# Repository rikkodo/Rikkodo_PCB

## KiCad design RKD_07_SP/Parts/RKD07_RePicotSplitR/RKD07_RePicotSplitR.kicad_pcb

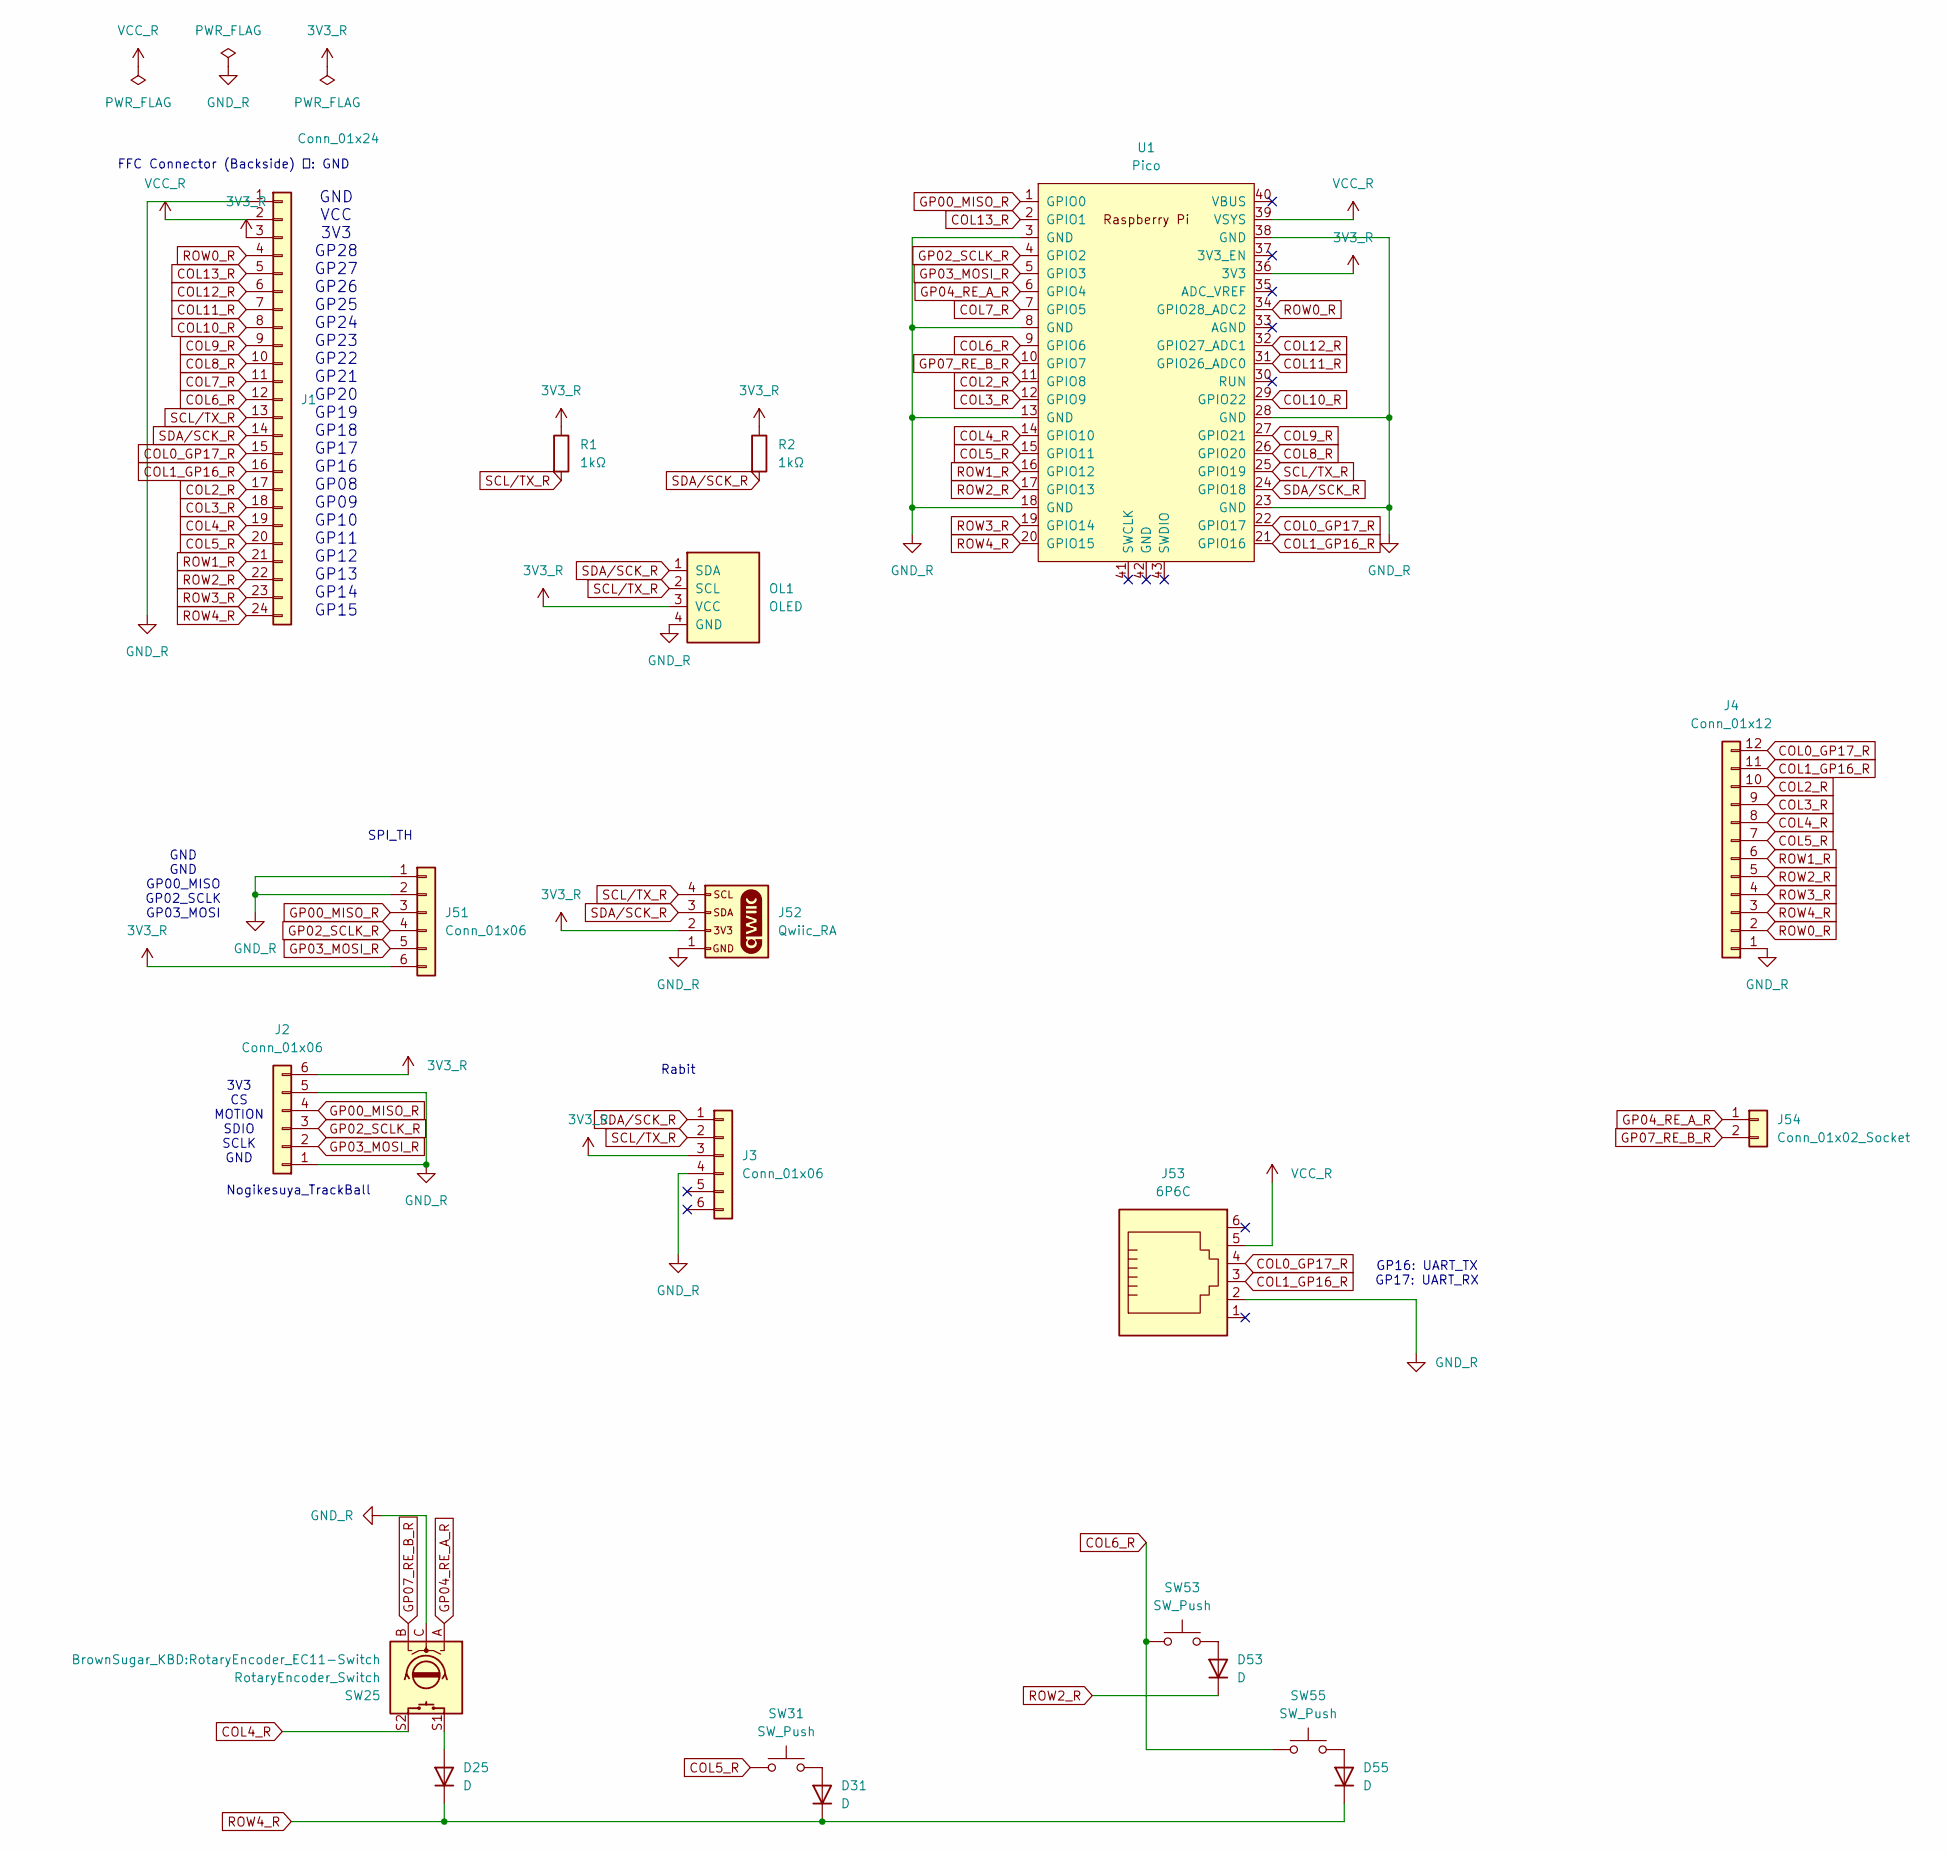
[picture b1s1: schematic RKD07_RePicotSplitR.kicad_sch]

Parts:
D25, D31, D53, D55: D; Diode_SMD
J1: Conn_01x24; Hirose_FH12-24S-0.5SH_1x24-1MP_P0.50mm_Horizontal
J2, J3: Conn_01x06; Hirose_FH12-6S-0.5SH_1x06-1MP_P0.50mm_Horizontal
J4: Conn_01x12; Hirose_FH12-12S-0.5SH_1x12-1MP_P0.50mm_Horizontal
J51: Conn_01x06; PinHeader_1x06_P2.54mm_Horizontal
J52: Qwiic_RA; JST_SMD_1.0mm-4_Black
J53: 6P6C; RJ12_Amphenol_54601-x06_Horizontal
J54: Conn_01x02_Socket; PinHeader_1x02_P2.54mm_Vertical
OL1: OLED; OLED_center_display
R1, R2: 1kΩ; R_0603_1608Metric
SW25: RotaryEncoder_Switch; RotaryEncoder_EC11-Switch
SW31, SW53, SW55: SW_Push; rkd_Asm_ChocV1V2_Hotswap_1u
U1: Pico; rkd_RPi_Pico_TH_NODBG

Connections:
3V3_R: J1.3, J2.6, J3.3, J51.6, J52.2, OL1.3 (VCC), R1.1, R2.1, U1.36 (3V3)
COL0_GP17_R: J1.15, J4.12, J53.4, U1.22 (GPIO17)
COL1_GP16_R: J1.16, J4.11, J53.3, U1.21 (GPIO16)
COL2_R: J1.17, J4.10, U1.11 (GPIO8)
COL3_R: J1.18, J4.9, U1.12 (GPIO9)
COL4_R: J1.19, J4.8, SW25.S2, U1.14 (GPIO10)
COL5_R: J1.20, J4.7, SW31.2, U1.15 (GPIO11)
COL6_R: J1.12, SW53.2, SW55.2, U1.9 (GPIO6)
COL7_R: J1.11, U1.7 (GPIO5)
COL8_R: J1.10, U1.26 (GPIO20)
COL9_R: J1.9, U1.27 (GPIO21)
COL10_R: J1.8, U1.29 (GPIO22)
COL11_R: J1.7, U1.31 (GPIO26_ADC0)
COL12_R: J1.6, U1.32 (GPIO27_ADC1)
COL13_R: J1.5, U1.2 (GPIO1)
GND_R: J1.1, J2.1, J2.5, J3.4, J4.1, J51.1, J51.2, J52.1, J53.2, OL1.4 (GND), SW25.C, U1.3 (GND), U1.8 (GND), U1.13 (GND), U1.18 (GND), U1.23 (GND), U1.28 (GND), U1.38 (GND)
GP00_MISO_R: J2.4, J51.3, U1.1 (GPIO0)
GP02_SCLK_R: J2.3, J51.4, U1.4 (GPIO2)
GP03_MOSI_R: J2.2, J51.5, U1.5 (GPIO3)
GP04_RE_A_R: J54.1, SW25.A, U1.6 (GPIO4)
GP07_RE_B_R: J54.2, SW25.B, U1.10 (GPIO7)
unnamed: D25.2 (A), SW25.S1
unnamed: D31.2 (A), SW31.1
unnamed: D53.2 (A), SW53.1
unnamed: D55.2 (A), SW55.1
ROW0_R: J1.4, J4.2, U1.34 (GPIO28_ADC2)
ROW1_R: J1.21, J4.6, U1.16 (GPIO12)
ROW2_R: D53.1 (K), J1.22, J4.5, U1.17 (GPIO13)
ROW3_R: J1.23, J4.4, U1.19 (GPIO14)
ROW4_R: D25.1 (K), D31.1 (K), D55.1 (K), J1.24, J4.3, U1.20 (GPIO15)
SCL/TX_R: J1.13, J3.2, J52.4, OL1.2 (SCL), R1.2, U1.25 (GPIO19)
SDA/SCK_R: J1.14, J3.1, J52.3, OL1.1 (SDA), R2.2, U1.24 (GPIO18)
VCC_R: J1.2, J53.5, U1.39 (VSYS)

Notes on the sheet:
GND GND GP00_MISO GP02_SCLK GP03_MOSI
Rabit
SPI_TH
GP16: UART_TX GP17: UART_RX
Nogikesuya_TrackBall
3V3 CS MOTION SDIO SCLK GND
FFC Connector (Backside) １: GND
GND VCC 3V3 GP28 GP27 GP26 GP25 GP24 GP23 GP22 GP21 GP20 GP19 GP18 GP17 GP16 GP08 GP09 GP10 GP11 GP12 GP13 GP14 GP15

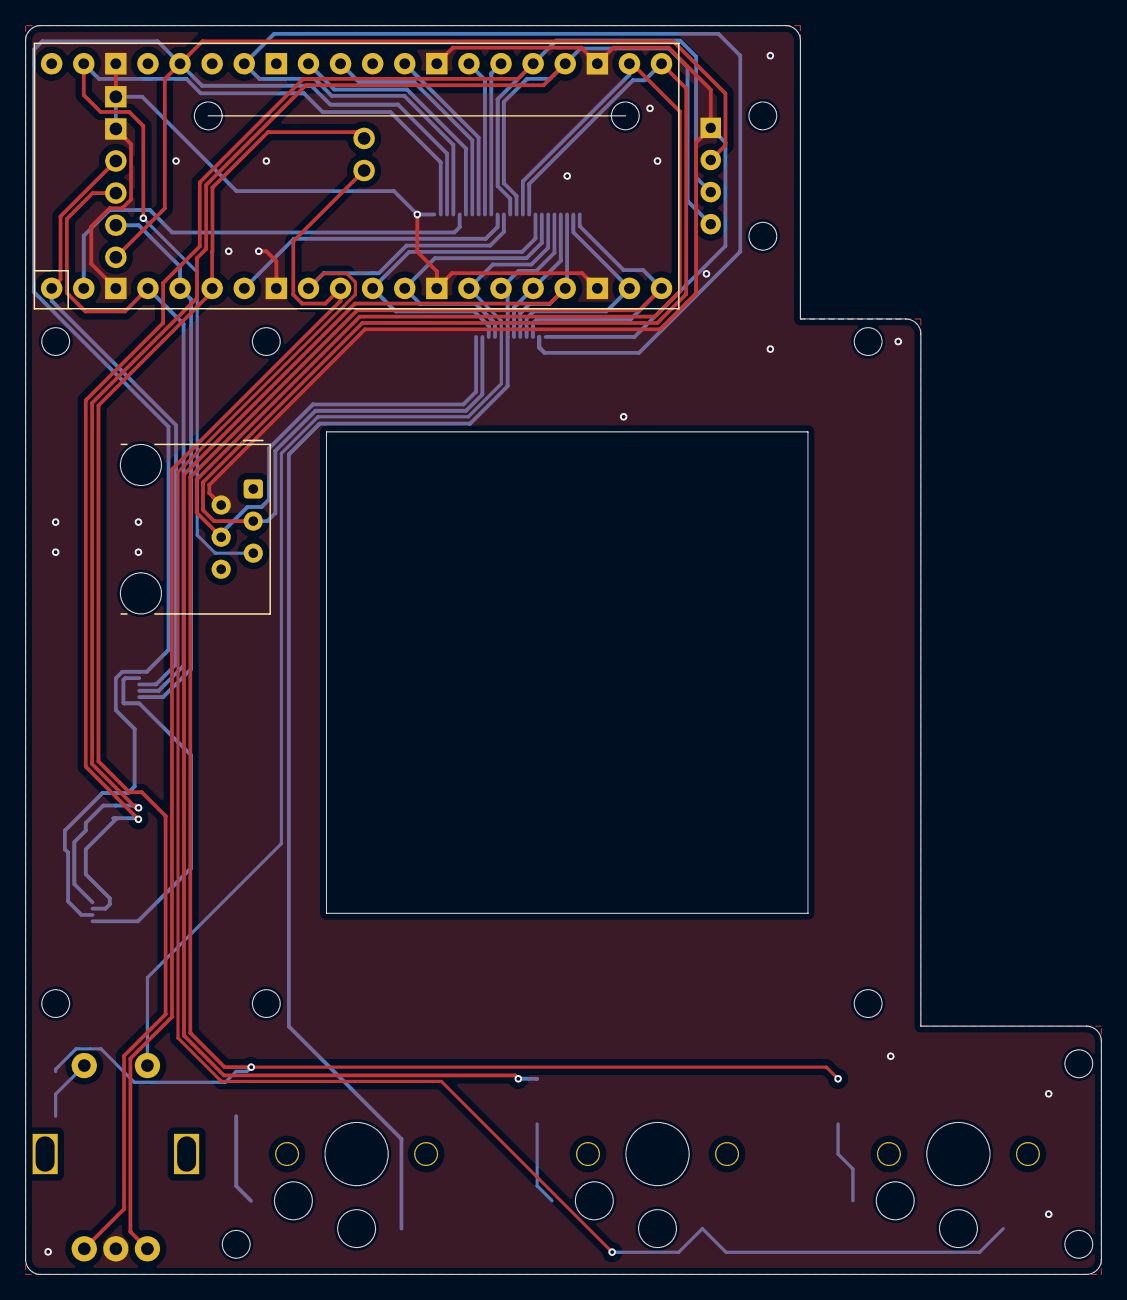
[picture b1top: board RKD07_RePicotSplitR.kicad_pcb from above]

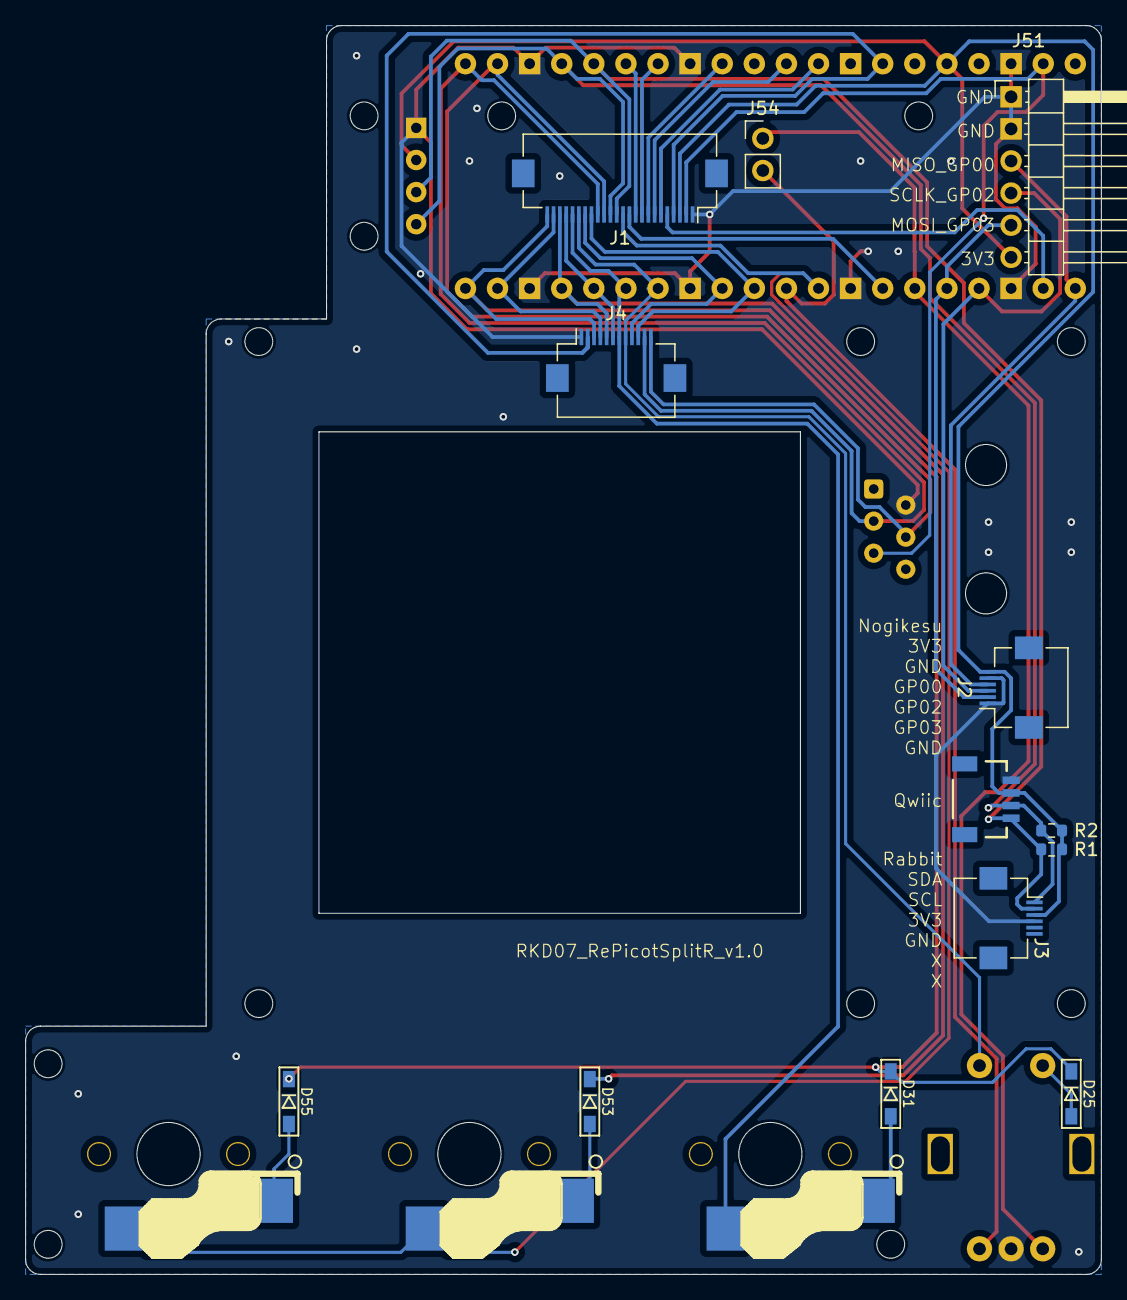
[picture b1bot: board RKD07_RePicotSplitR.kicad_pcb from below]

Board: 2 copper layers, 85.1 x 98.8 mm, 31 parts (9 on the bottom side), 33 nets.

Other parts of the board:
Point1: Guard_Screw_Hall; rkd_Guard_Screw_Hall
Ref**: Val**; m2_Screw_Hole
Ref**#2, Ref**#3, Ref**#4, Ref**#5, Ref**#6, Ref**#7, Ref**#8, Ref**#9: Val**; m2_Screw_Hole
UnifiedW**: rkd_unified_wid_BTM

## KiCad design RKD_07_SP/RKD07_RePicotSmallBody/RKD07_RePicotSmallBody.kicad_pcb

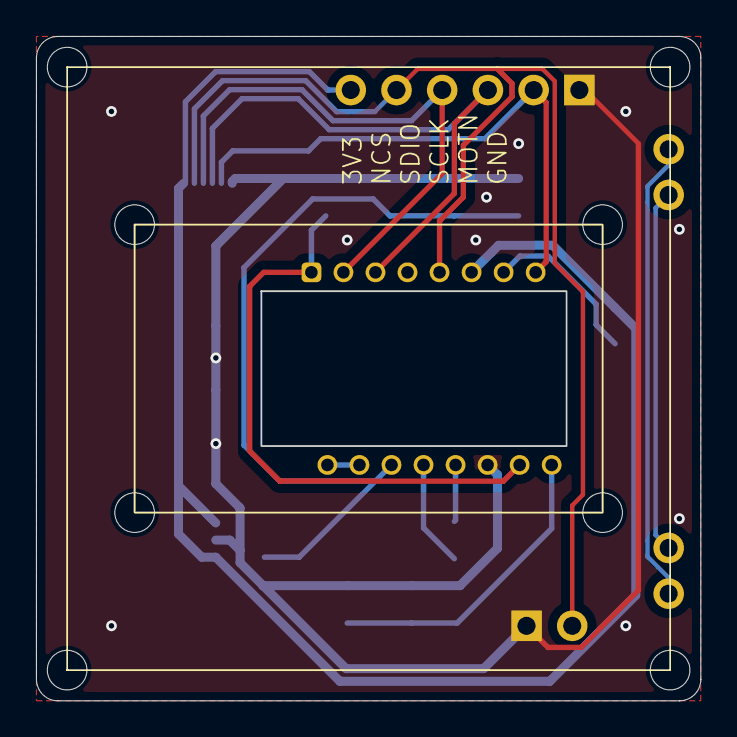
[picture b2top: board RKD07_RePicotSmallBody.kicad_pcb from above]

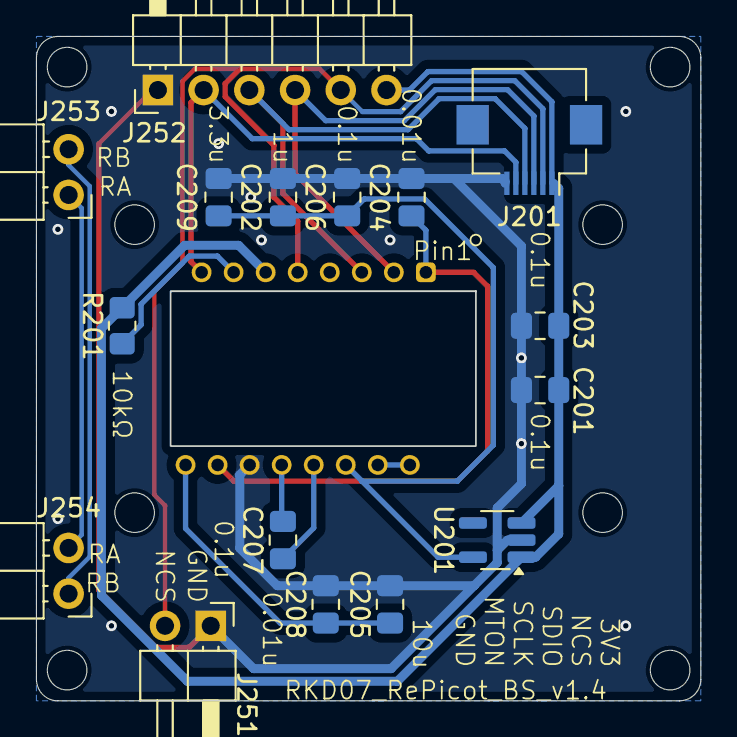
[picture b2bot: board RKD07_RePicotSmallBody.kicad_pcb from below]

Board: 2 copper layers, 36.9 x 36.9 mm, 18 parts (16 on the bottom side), 15 nets.

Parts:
C201, C203, C206, C207: 0.1uF X7R; C_0805_2012Metric_Pad1.18x1.45mm_HandSolder
C202: 1uF; C_0805_2012Metric_Pad1.18x1.45mm_HandSolder
C204, C208: 0.01uF X7R; C_0805_2012Metric_Pad1.18x1.45mm_HandSolder
C205: 10uF X7R; C_0805_2012Metric_Pad1.18x1.45mm_HandSolder
C209: 3.3uF/16V; C_0805_2012Metric_Pad1.18x1.45mm_HandSolder
J201: Conn_01x06; Hirose_FH12-6S-0.5SH_1x06-1MP_P0.50mm_Horizontal
J251, J253, J254: Conn_01x02_Socket; PinHeader_1x02_P2.54mm_Horizontal
J252: Conn_01x06; PinHeader_1x06_P2.54mm_Horizontal
Picot**: rkd_picot5400_BTM
R201: 10k; R_0805_2012Metric_Pad1.20x1.40mm_HandSolder
U201: TLV70019DDCR; SOT-23-5_HandSoldering
U202: PMW3610DM-SUDU

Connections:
1V9_E: C202.1, C206.1, C209.1, U201.5 (OUT), U202.14 (VDD)
3V3_E: C201.1, C203.1, J201.1, J252.6, R201.2, U201.1 (IN), U201.3 (EN), U202.6 (VDDIO)
GND_E: C201.2, C202.2, C203.2, C204.2, C205.2, C206.2, C208.2, C209.2, J201.6, J251.1, J252.1, U201.2 (GND), U202.11 (GND)
GP00_MISO_E: J201.3, J252.4, U202.2 (SDIO)
GP02_SCLK_E: J201.4, J252.3, U202.3 (SCLK)
GP03_MOSI_E: J201.5, J252.2, U202.8 (MOTION)
GP04_E: J253.1, J254.2
GP07_E: J253.2, J254.1
NCS_E: J201.2, J251.2, J252.5, U202.5 (NCS)
unnamed: C204.1, U202.1 (+VCSEL), U202.10 (PASS_T)
unnamed: U202.15 (XYLASER), U202.16 (-VCSEL)
unnamed: C207.1, U202.13 (CN)
unnamed: C207.2, U202.12 (CP)
unnamed: R201.1, U202.7 (NRESET)
unnamed: C205.1, C208.1, U202.9 (VCP)

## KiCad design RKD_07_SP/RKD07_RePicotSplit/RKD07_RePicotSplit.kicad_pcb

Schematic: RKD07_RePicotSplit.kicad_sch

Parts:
C201, C203, C206, C207: 0.1uF X7R; C_0805_2012Metric_Pad1.18x1.45mm_HandSolder
C202: 1uF; C_0805_2012Metric_Pad1.18x1.45mm_HandSolder
C204, C208: 0.01uF X7R; C_0805_2012Metric_Pad1.18x1.45mm_HandSolder
C205: 10uF X7R; C_0805_2012Metric_Pad1.18x1.45mm_HandSolder
C209: 3.3uF/16V; C_0805_2012Metric_Pad1.18x1.45mm_HandSolder
D25, D31, D53, D55: D; Diode_SMD
J1, J101: Conn_01x24; Hirose_FH12-24S-0.5SH_1x24-1MP_P0.50mm_Horizontal
J2, J3, J5, J102, J104, J201: Conn_01x06; Hirose_FH12-6S-0.5SH_1x06-1MP_P0.50mm_Horizontal
J4, J103: Conn_01x12; Hirose_FH12-12S-0.5SH_1x12-1MP_P0.50mm_Horizontal
J51: Conn_01x06; PinHeader_1x06_P2.54mm_Horizontal
J52: Qwiic_RA; JST_SMD_1.0mm-4_Black
J53, J153: 6P6C; RJ12_Amphenol_54601-x06_Horizontal
J54, J154, J251, J253, J254: Conn_01x02_Socket; PinHeader_1x02_P2.54mm_Vertical
J151: Conn_01x06; PinHeader_1x08_P2.54mm_Vertical
J152: Conn_01x08; PinHeader_1x08_P2.54mm_Vertical
J252: Conn_01x06; PinHeader_1x06_P2.54mm_Vertical
OL1, OL101: OLED; OLED_center_display
R1, R2: 1kΩ; R_0603_1608Metric
R201: 10k; R_0805_2012Metric_Pad1.20x1.40mm_HandSolder
SW25: RotaryEncoder_Switch; RotaryEncoder_EC11-Switch
SW31, SW53, SW55: SW_Push; rkd_Asm_ChocV1V2_Hotswap_1u
U1, U101: Pico; rkd_RPi_Pico_TH_NODBG
U201: TLV70019DDCR; SOT-23-5_HandSoldering
U202: PMW3610DM-SUDU

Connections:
1V9_E: C202.1, C206.1, C209.1, U201.5 (OUT), U202.14 (VDD)
3V3_E: C201.1, C203.1, J201.1, J252.6, R201.2, U201.1 (IN), U201.3 (EN), U202.6 (VDDIO)
3V3_L: J101.3, J102.6, J151.8, J152.7, OL101.3 (VCC), U101.36 (3V3)
3V3_R: J1.3, J2.6, J3.3, J51.6, J52.2, OL1.3 (VCC), R1.1, R2.1, U1.36 (3V3)
COL0_GP17_R: J1.15, J4.12, J53.4, U1.22 (GPIO17)
COL0_L: J101.15, U101.7 (GPIO5)
COL1_GP16_R: J1.16, J4.11, J53.3, U1.21 (GPIO16)
COL1_L: J101.16, U101.9 (GPIO6)
COL2_L: J101.17, U101.11 (GPIO8)
COL2_R: J1.17, J4.10, U1.11 (GPIO8)
COL3_L: J101.18, U101.12 (GPIO9)
COL3_R: J1.18, J4.9, U1.12 (GPIO9)
COL4_L: J101.19, U101.14 (GPIO10)
COL4_R: J1.19, J4.8, SW25.S2, U1.14 (GPIO10)
COL5_L: J101.20, U101.15 (GPIO11); also elsewhere on the board
COL5_R: J1.20, J4.7, SW31.2, U1.15 (GPIO11)
COL6_GP16_L: J101.12, J103.11, J153.3, U101.21 (GPIO16)
COL6_R: J1.12, J5.1, SW53.2, SW55.2, U1.9 (GPIO6)
COL7_GP17_L: J101.11, J103.12, J153.4, U101.22 (GPIO17)
COL7_R: J1.11, J5.2, U1.7 (GPIO5)
COL8_L: J101.10, J103.7, J152.2, U101.26 (GPIO20)
COL8_R: J1.10, U1.26 (GPIO20)
COL9_L: J101.9, J103.8, J152.3, U101.27 (GPIO21)
COL9_R: J1.9, U1.27 (GPIO21)
COL10_L: J101.8, J104.3, J152.4, U101.29 (GPIO22)
COL10_R: J1.8, J5.3, U1.29 (GPIO22)
COL11_L: J101.7, J103.9, J152.5, U101.31 (GPIO26_ADC0)
COL11_R: J1.7, U1.31 (GPIO26_ADC0)
COL12_L: J101.6, J103.10, J152.6, U101.32 (GPIO27_ADC1)
COL12_R: J1.6, U1.32 (GPIO27_ADC1)
COL13_GP01_NCS_L: J101.5, J104.2, J151.4, U101.2 (GPIO1)
COL13_R: J1.5, U1.2 (GPIO1)
GND_E: C201.2, C202.2, C203.2, C204.2, C205.2, C206.2, C208.2, C209.2, J201.6, J251.1, J252.1, U201.2 (GND), U202.11 (GND)
GND_L: J101.1, J102.1, J102.5, J103.1, J104.6, J151.1, J151.2, J151.3, J152.1, J153.2, OL101.4 (GND), U101.3 (GND), U101.8 (GND), U101.13 (GND), U101.18 (GND), U101.23 (GND), U101.28 (GND), U101.38 (GND); also elsewhere on the board
GND_R: J1.1, J2.1, J2.5, J3.4, J4.1, J5.6, J51.1, J51.2, J52.1, J53.2, OL1.4 (GND), SW25.C, U1.3 (GND), U1.8 (GND), U1.13 (GND), U1.18 (GND), U1.23 (GND), U1.28 (GND), U1.38 (GND)
GP00_MISO_E: J201.3, J252.4, U202.2 (SDIO)
GP00_MISO_L: J102.4, J151.5, U101.1 (GPIO0)
GP00_MISO_R: J2.4, J51.3, U1.1 (GPIO0)
GP02_SCLK_E: J201.4, J252.3, U202.3 (SCLK)
GP02_SCLK_L: J102.3, J151.6, U101.4 (GPIO2)
GP02_SCLK_R: J2.3, J51.4, U1.4 (GPIO2)
GP03_MOSI_E: J201.5, J252.2, U202.8 (MOTION)
GP03_MOSI_L: J102.2, J151.7, U101.5 (GPIO3)
GP03_MOSI_R: J2.2, J51.5, U1.5 (GPIO3)
GP04_E: J253.1, J254.2
GP04_L: J104.5, J154.1, U101.6 (GPIO4); also elsewhere on the board
GP04_RE_A_R: J5.5, J54.1, SW25.A, U1.6 (GPIO4)
GP07_E: J253.2, J254.1
GP07_L: J104.4, J154.2, U101.10 (GPIO7); also elsewhere on the board
GP07_RE_B_R: J5.4, J54.2, SW25.B, U1.10 (GPIO7)
NCS_E: J201.2, J251.2, J252.5, U202.5 (NCS)
unnamed: D25.2 (A), SW25.S1
unnamed: D31.2 (A), SW31.1
unnamed: D53.2 (A), SW53.1
unnamed: D55.2 (A), SW55.1
unnamed: C204.1, U202.1 (+VCSEL), U202.10 (PASS_T)
unnamed: U202.15 (XYLASER), U202.16 (-VCSEL)
unnamed: C207.1, U202.13 (CN)
unnamed: C207.2, U202.12 (CP)
unnamed: R201.1, U202.7 (NRESET)
unnamed: C205.1, C208.1, U202.9 (VCP)
ROW0_L: J101.4, J103.2, U101.34 (GPIO28_ADC2)
ROW0_R: J1.4, J4.2, U1.34 (GPIO28_ADC2)
ROW1_L: J101.21, J103.6, U101.16 (GPIO12)
ROW1_R: J1.21, J4.6, U1.16 (GPIO12)
ROW2_L: J101.22, J103.5, U101.17 (GPIO13)
ROW2_R: D53.1 (K), J1.22, J4.5, U1.17 (GPIO13)
ROW3_L: J101.23, J103.4, U101.19 (GPIO14)
ROW3_R: J1.23, J4.4, U1.19 (GPIO14)
ROW4_L: J101.24, J103.3, U101.20 (GPIO15); also elsewhere on the board
ROW4_R: D25.1 (K), D31.1 (K), D55.1 (K), J1.24, J4.3, U1.20 (GPIO15)
SCL/TX_L: J101.13, OL101.2 (SCL), U101.25 (GPIO19)
SCL/TX_R: J1.13, J3.2, J52.4, OL1.2 (SCL), R1.2, U1.25 (GPIO19)
SDA/SCK_L: J101.14, OL101.1 (SDA), U101.24 (GPIO18)
SDA/SCK_R: J1.14, J3.1, J52.3, OL1.1 (SDA), R2.2, U1.24 (GPIO18)
VCC_L: J101.2, J152.8, J153.5, U101.39 (VSYS)
VCC_R: J1.2, J53.5, U1.39 (VSYS)

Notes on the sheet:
SPI_TH
Nogikesuya_TrackBall
3V3 NCS SDIO SCLK MOTION GND
3V3 CS MOTION SDIO SCLK GND
GND GND GP00_MISO GP02_SCLK GP03_MOSI
Rabit
GND MOTION SCLK SDIO NCS 3V3
GND GP01_NCS GP00_MISO GP02_SCLK GP03_MOSI
GP16: UART_TX GP17: UART_RX
Receive
FFC Connector (Backside) １: GND
GND VCC 3V3 GP28 GP27 GP26 GP25 GP24 GP23 GP22 GP21 GP20 GP19 GP18 GP17 GP16 GP08 GP09 GP10 GP11 GP12 GP13 GP14 GP15

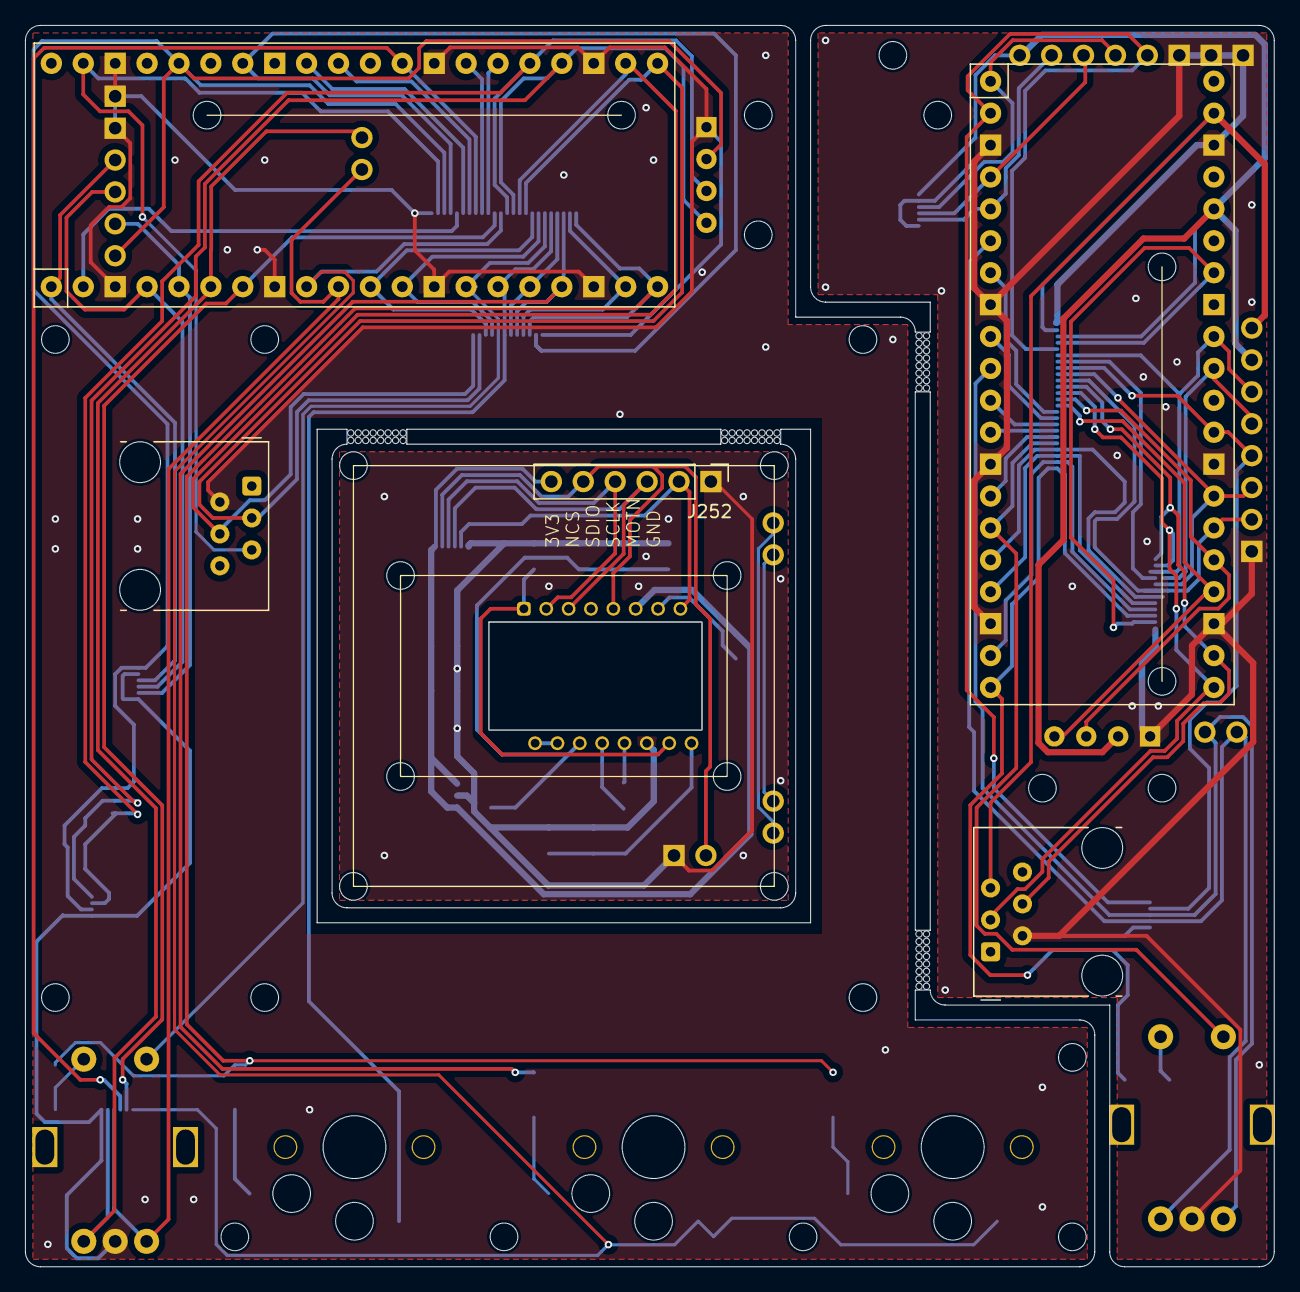
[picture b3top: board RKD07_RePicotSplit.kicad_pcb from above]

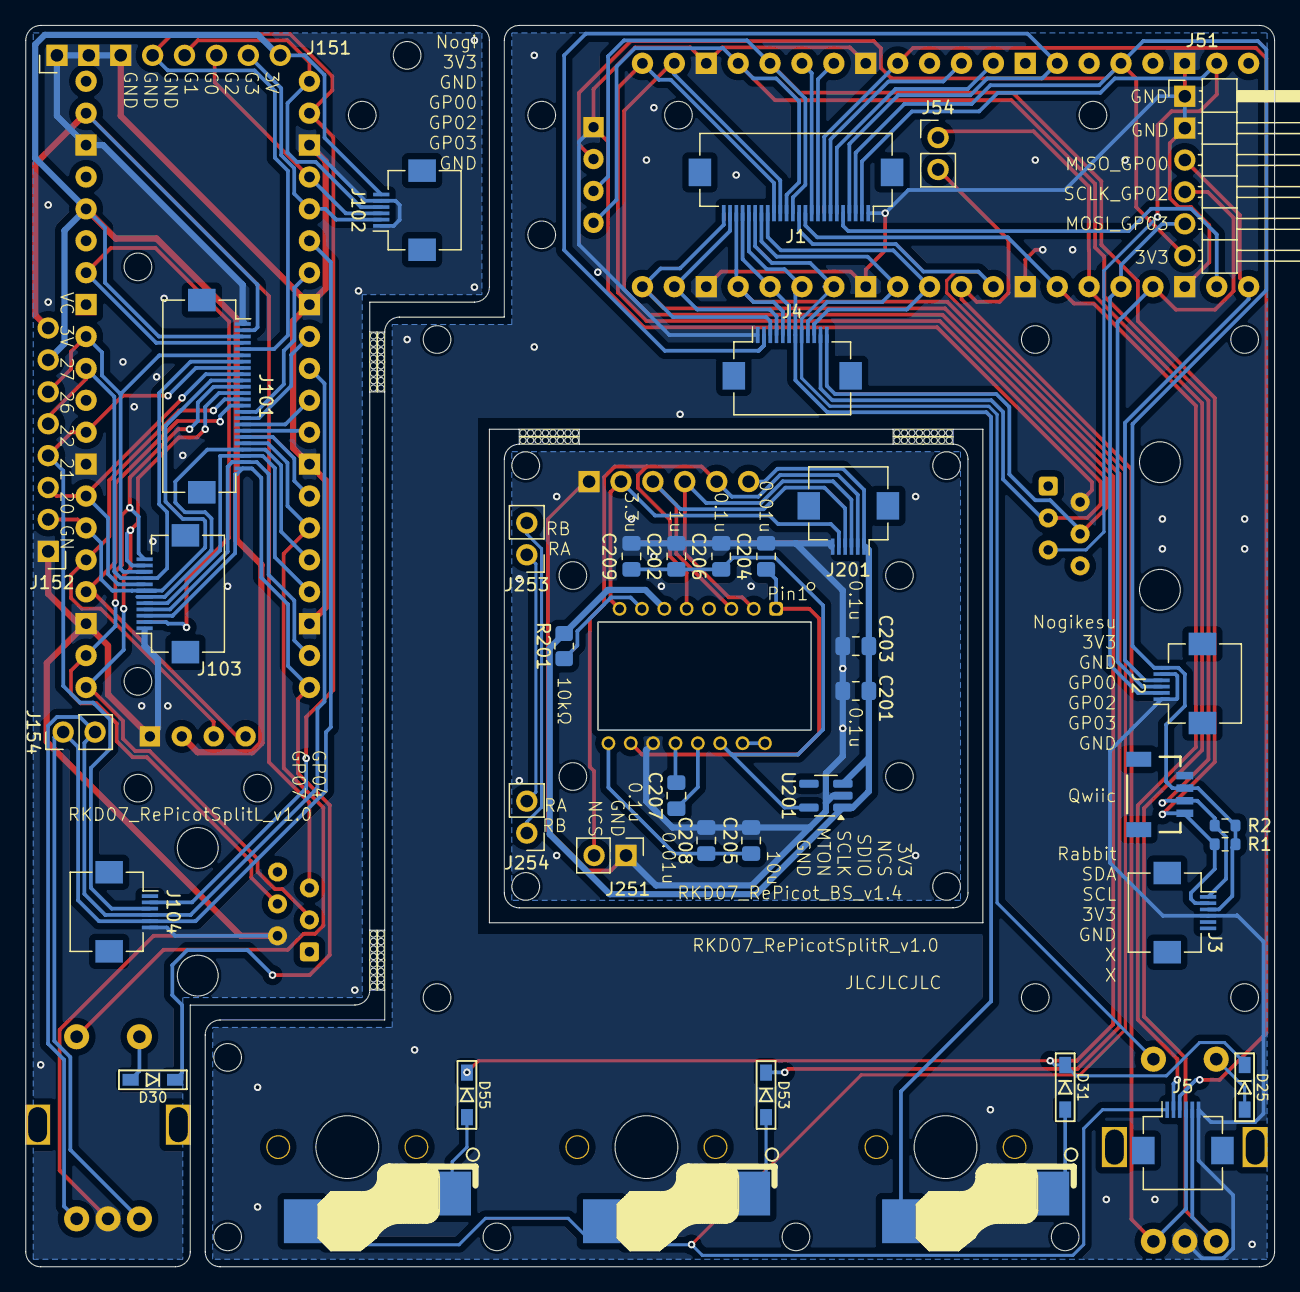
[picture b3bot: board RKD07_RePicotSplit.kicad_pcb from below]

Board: 2 copper layers, 99.4 x 98.8 mm, 68 parts (32 on the bottom side), 78 nets.

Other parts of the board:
D30: D; Diode_SMD
Picot**: rkd_picot5400_BTM
Point1, Point1#2: Guard_Screw_Hall; rkd_Guard_Screw_Hall
Ref**: Val**; m2_Screw_Hole
Ref**#2, Ref**#3, Ref**#4, Ref**#5, Ref**#6, Ref**#7, Ref**#8, Ref**#9, Ref**#10, Ref**#11, Ref**#12, Ref**#13: Val**; m2_Screw_Hole
SW30: RotaryEncoder_Switch; RotaryEncoder_EC11-Switch
UnifiedW**: rkd_unified_wid_BTM
UnifiedW**#2: rkd_unified_wid_BTM

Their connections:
COL5_L: SW30.S2; also elsewhere on the board
GND_L: SW30.C; also elsewhere on the board
GP04_L: SW30.A; also elsewhere on the board
GP07_L: SW30.B; also elsewhere on the board
unnamed: D30.2 (A), SW30.S1
ROW4_L: D30.1 (K); also elsewhere on the board

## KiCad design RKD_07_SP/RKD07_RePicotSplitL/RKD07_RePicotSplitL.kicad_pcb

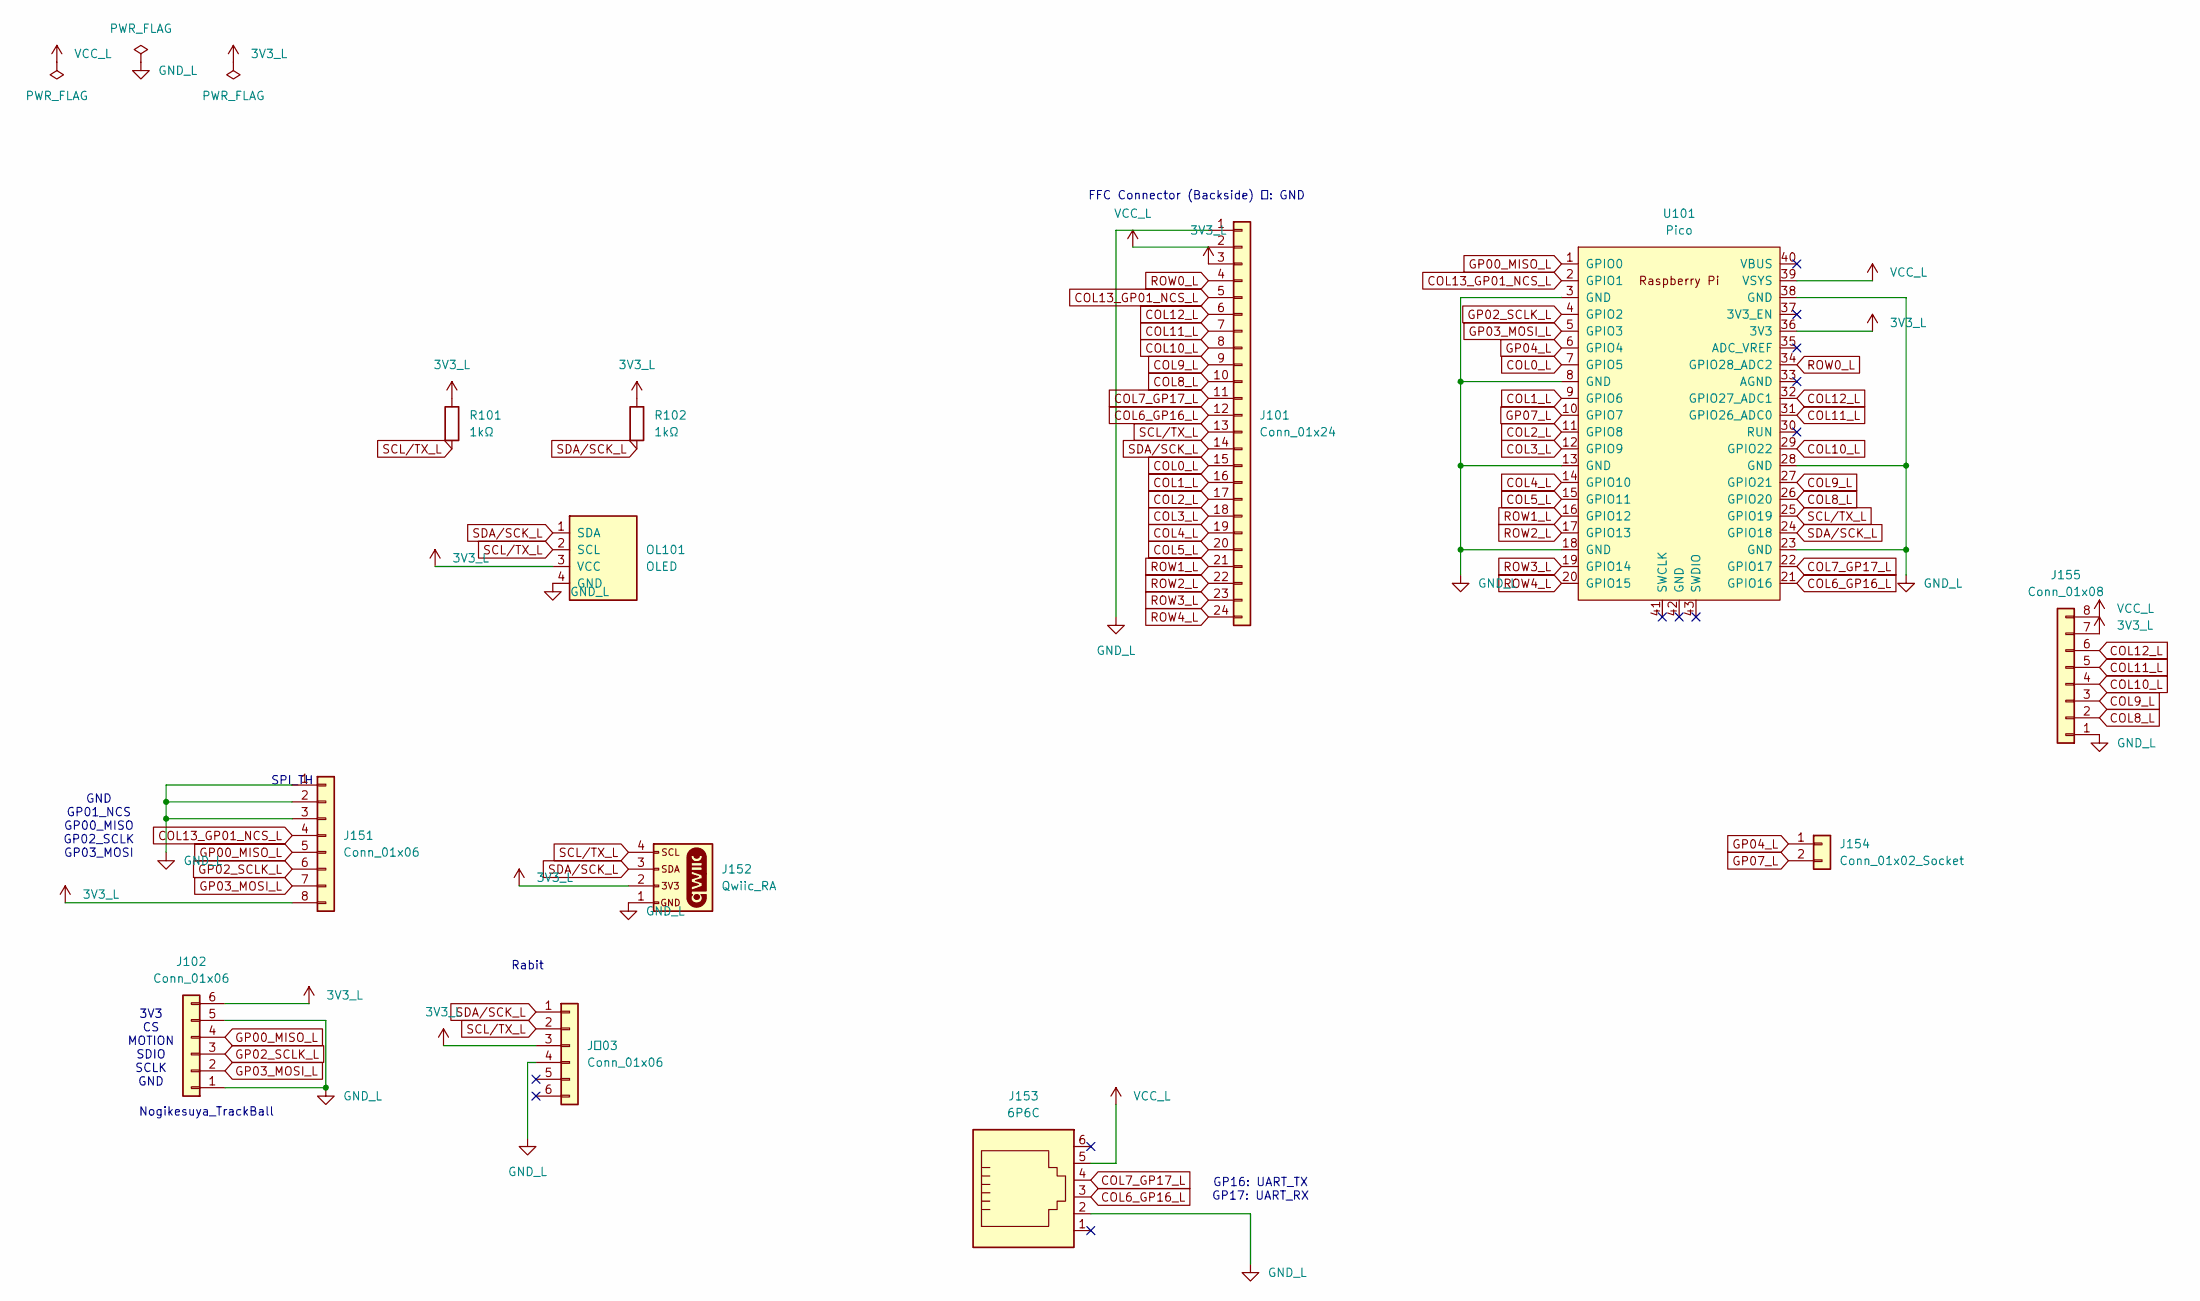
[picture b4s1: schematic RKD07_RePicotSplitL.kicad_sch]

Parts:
J101: Conn_01x24; Hirose_FH12-24S-0.5SH_1x24-1MP_P0.50mm_Horizontal
J102, J１03: Conn_01x06; Hirose_FH12-6S-0.5SH_1x06-1MP_P0.50mm_Horizontal
J151: Conn_01x06; PinHeader_1x08_P2.54mm_Vertical
J152: Qwiic_RA; JST_SMD_1.0mm-4_Black
J153: 6P6C; RJ12_Amphenol_54601-x06_Horizontal
J154: Conn_01x02_Socket; PinHeader_1x02_P2.54mm_Vertical
J155: Conn_01x08; PinHeader_1x08_P2.54mm_Vertical
OL101: OLED; OLED_center_display
R101, R102: 1kΩ; R_0603_1608Metric
U101: Pico; rkd_RPi_Pico_TH_NODBG

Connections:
3V3_L: J101.3, J102.6, J151.8, J152.2, J155.7, J１03.3, OL101.3 (VCC), R101.1, R102.1, U101.36 (3V3)
COL0_L: J101.15, U101.7 (GPIO5)
COL1_L: J101.16, U101.9 (GPIO6)
COL2_L: J101.17, U101.11 (GPIO8)
COL3_L: J101.18, U101.12 (GPIO9)
COL4_L: J101.19, U101.14 (GPIO10)
COL5_L: J101.20, U101.15 (GPIO11)
COL6_GP16_L: J101.12, J153.3, U101.21 (GPIO16)
COL7_GP17_L: J101.11, J153.4, U101.22 (GPIO17)
COL8_L: J101.10, J155.2, U101.26 (GPIO20)
COL9_L: J101.9, J155.3, U101.27 (GPIO21)
COL10_L: J101.8, J155.4, U101.29 (GPIO22)
COL11_L: J101.7, J155.5, U101.31 (GPIO26_ADC0)
COL12_L: J101.6, J155.6, U101.32 (GPIO27_ADC1)
COL13_GP01_NCS_L: J101.5, J151.4, U101.2 (GPIO1)
GND_L: J101.1, J102.1, J102.5, J151.1, J151.2, J151.3, J152.1, J153.2, J155.1, J１03.4, OL101.4 (GND), U101.3 (GND), U101.8 (GND), U101.13 (GND), U101.18 (GND), U101.23 (GND), U101.28 (GND), U101.38 (GND)
GP00_MISO_L: J102.4, J151.5, U101.1 (GPIO0)
GP02_SCLK_L: J102.3, J151.6, U101.4 (GPIO2)
GP03_MOSI_L: J102.2, J151.7, U101.5 (GPIO3)
GP04_L: J154.1, U101.6 (GPIO4)
GP07_L: J154.2, U101.10 (GPIO7)
ROW0_L: J101.4, U101.34 (GPIO28_ADC2)
ROW1_L: J101.21, U101.16 (GPIO12)
ROW2_L: J101.22, U101.17 (GPIO13)
ROW3_L: J101.23, U101.19 (GPIO14)
ROW4_L: J101.24, U101.20 (GPIO15)
SCL/TX_L: J101.13, J152.4, J１03.2, OL101.2 (SCL), R101.2, U101.25 (GPIO19)
SDA/SCK_L: J101.14, J152.3, J１03.1, OL101.1 (SDA), R102.2, U101.24 (GPIO18)
VCC_L: J101.2, J153.5, J155.8, U101.39 (VSYS)

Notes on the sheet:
GND GP01_NCS GP00_MISO GP02_SCLK GP03_MOSI
FFC Connector (Backside) １: GND
SPI_TH
GP16: UART_TX GP17: UART_RX
Nogikesuya_TrackBall
3V3 CS MOTION SDIO SCLK GND
Rabit
